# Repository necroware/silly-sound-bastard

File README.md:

# Silly Sound Bastard

It is yet another clone of the well known Covox Speech Thing. I wanted to get
some practice in EDA and what is one of the simplest part to make, which you
could have fun with? If you are in retro community, you would understand, why it
was a Covox clone.

## What is special about it?

Well, it is still a simple Covox clone. However, I wanted to make something
brute, what you can solder easily, using some through holes parts, but still
with some space for experiments. So I made it with a quad switch, three of which
can be used to control bypass capacitors, to play with low-pass filtering and 
one for switching between mono and (fake-)stereo sound.

## How does it sound?

I made a [video](https://youtu.be/DKLKtH_rQJU) on my Youtube chanel about this
Covox clone.

## Bill of materials

I have a good news for someone, who is especially keen to solder. Instead of
using two types of resistors with 1/2 relation, I just used all the same types,
but doubbled one row to maintain the relation. This way you don't need to search
for resistors with a proper 1/2 relation, but just can take any resistors, you
have at hand. The parallel port connector is not a through hole part, but rather
a normal connector, like used in any printer cable. It is quite easy to find and
can be directly soldered to the edge of the PCB.

Part   | Count | Remarks
-------|-------| ----------
R1..R26|26x    | 7.5kOhm resistor
C1     |1x     | 0.01uF tantalum capacitor
C2     |1x     | 0.1uF tantalum capacitor
C3     |1x     | 1.0uF tantalum capacitor
C4     |1x     | 1.0uF electrolytic capacitor
SW1    |1x     | Quad-Switch (like LCSC C559139)
AUDIO1 |1x     | 3,5mm Audio jack port (like LCSC C145816)
LPT    |1x     | DB25 parallel port M-plug

## There is a long and a short variants?

Yes, I actually made two variants. The long board has switches, variable low 
pass filtering and uses three rows of same resistors. If you are not interested 
in all of that, you have a set of two types of resistors with a proper 1/2 
relation and space is more important for you, then take the short variant. You
will need less parts and get a more compact solution.

Part      | Count | Remarks
----------|-------| ----------
R1..R8,R17|9x     | 15kOhm resistor
R9..R16   |8x     | 7.5kOhm resistor
C1        |1x     | 0.1uF electrolytic capacitor
C2        |1x     | 1uF tantalum or electrolytic capacitor
AUDIO1    |1x     | 3,5mm Audio jack port (like LCSC C18166)
LPT       |1x     | DB25 parallel port M-plug

## How did I make it?

I used [EasyEDA](https://easyeda.com/) to create this PCBs. If you want to
derive from this work, you can find all the files in the project subfolders of
the boards. To order the parts I used [LCSC](https://lcsc.com).

## Possible modifications

It is reasonable to play around with another resistors and filter capacitors.
The higher the resistors value, the less noise you will get through the parallel
port. However, this also would mean less power on the audio output and necessity
of an amplifier. If you want to use passive headphones, try to go with lower
resistance. I used 1kOhm (and 2kOhm) resistors and the audio quality was still
quite good. Also the low pass filter capacitors are variable. It depends very
much on the speakers, what's the best, but I found, that it's not worth it to go
over 1uF. Even then, filtering starts to be very aggressive. The higher resitor
values you take, the lower capacitor values you should need.

## Links
* [Some theory by Eugeny Brychkov](http://kb.gr8bit.ru/KB0010/GR8BIT-KB0010-Adding-multimedia-capability-covox-device.html)

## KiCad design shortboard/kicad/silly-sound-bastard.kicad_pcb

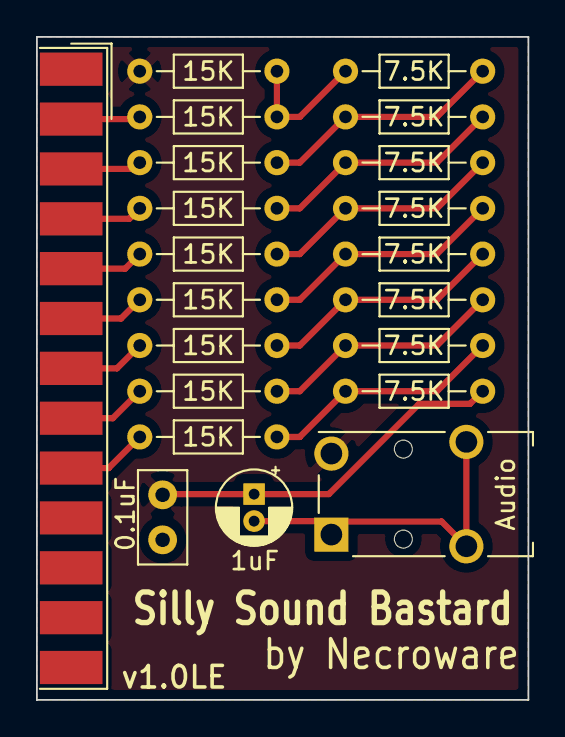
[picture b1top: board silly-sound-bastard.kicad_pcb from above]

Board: 2 copper layers, 27.3 x 36.8 mm, 21 parts (0 on the bottom side), 19 nets.

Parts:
C1: 0.1uF; C_Disc_D5.0mm_W2.5mm_P2.50mm
C2: 1uF; CP_Radial_D4.0mm_P1.50mm
J1: LPT; DSUB-25_Male_EdgeMount_P2.77mm
J2: Audio; Jack_3.5mm_Switronic_ST-005-G_horizontal
R1, R2, R3, R4, R5, R6, R7, R8, R9: 15K; R_Axial_DIN0204_L3.6mm_D1.6mm_P7.62mm_Horizontal
R10, R11, R12, R13, R14, R15, R16, R17: 7.5K; R_Axial_DIN0204_L3.6mm_D1.6mm_P7.62mm_Horizontal

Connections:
GND: C1.2, J1.18, J1.19, J1.20, J1.21, J1.22, J1.23, J1.24, J1.25, J2.S, R1.1
unnamed: C1.1, C2.1, R17.2
unnamed: C2.2, J2.R, J2.T
unnamed: J1.2, R2.1
unnamed: J1.3, R3.1
unnamed: J1.4, R4.1
unnamed: J1.5, R5.1
unnamed: J1.6, R6.1
unnamed: J1.7, R7.1
unnamed: J1.8, R8.1
unnamed: J1.9, R9.1
unnamed: R1.2, R2.2, R10.1
unnamed: R3.2, R10.2, R11.1
unnamed: R4.2, R11.2, R12.1
unnamed: R5.2, R12.2, R13.1
unnamed: R6.2, R13.2, R14.1
unnamed: R7.2, R14.2, R15.1
unnamed: R8.2, R15.2, R16.1
unnamed: R9.2, R16.2, R17.1

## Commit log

2020-10-23 Fixed version of short board
2020-10-23 Added more documentation
2020-11-04 Set standard resistors and adapt capacitors
2020-11-04 Add possible mods to readme
2020-11-04 Add youtube link
2020-11-27 Add shortboard version in kicad
2021-01-29 Add theory link
